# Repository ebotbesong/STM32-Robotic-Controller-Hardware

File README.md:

# STM32 Robotic Controller Hardware
This project introduces the design of a PCB board layout for robotics applications. The microcontroller used in the board design is the STM32F103C8T6. The STM32F103C8T6 is a medium density performance line ARM Cortex-M3 32bit microcontroller in the 48 pin LQFP package. It incorporates high performance RISC core with up to 72MHz operating frequency, high speed embedded memories, extensive range of enhanced I/Os and peripherals connected buses.

The designed board can be use as an alternative to the well known and documented Arduino and raspberry pie hardware. Also, the provided design can be modify to add more memory if needed. This however increases the complexity of the hardware.

## Isometric view
The MicroUSB is used but this can be change to USB type-C which is becoming the de facto standard nowadays.

 ## Top view
 There is provision for I2C and UART connector in the design. Therefore both the I2C and UART bus lines can be used for control interfaces.

## The PCB layout
The PCB layout was done using the KICAD EDA version 5.61 and the design is opensource. All design files are provided for download and can be found in the folder "docs" of the main repository shown above. Advanced version of the KICAD EDA can also be used to open the design files.

The project website is  https://ebotbesong.github.io/STM32-Robotic-Controller-Hardware/

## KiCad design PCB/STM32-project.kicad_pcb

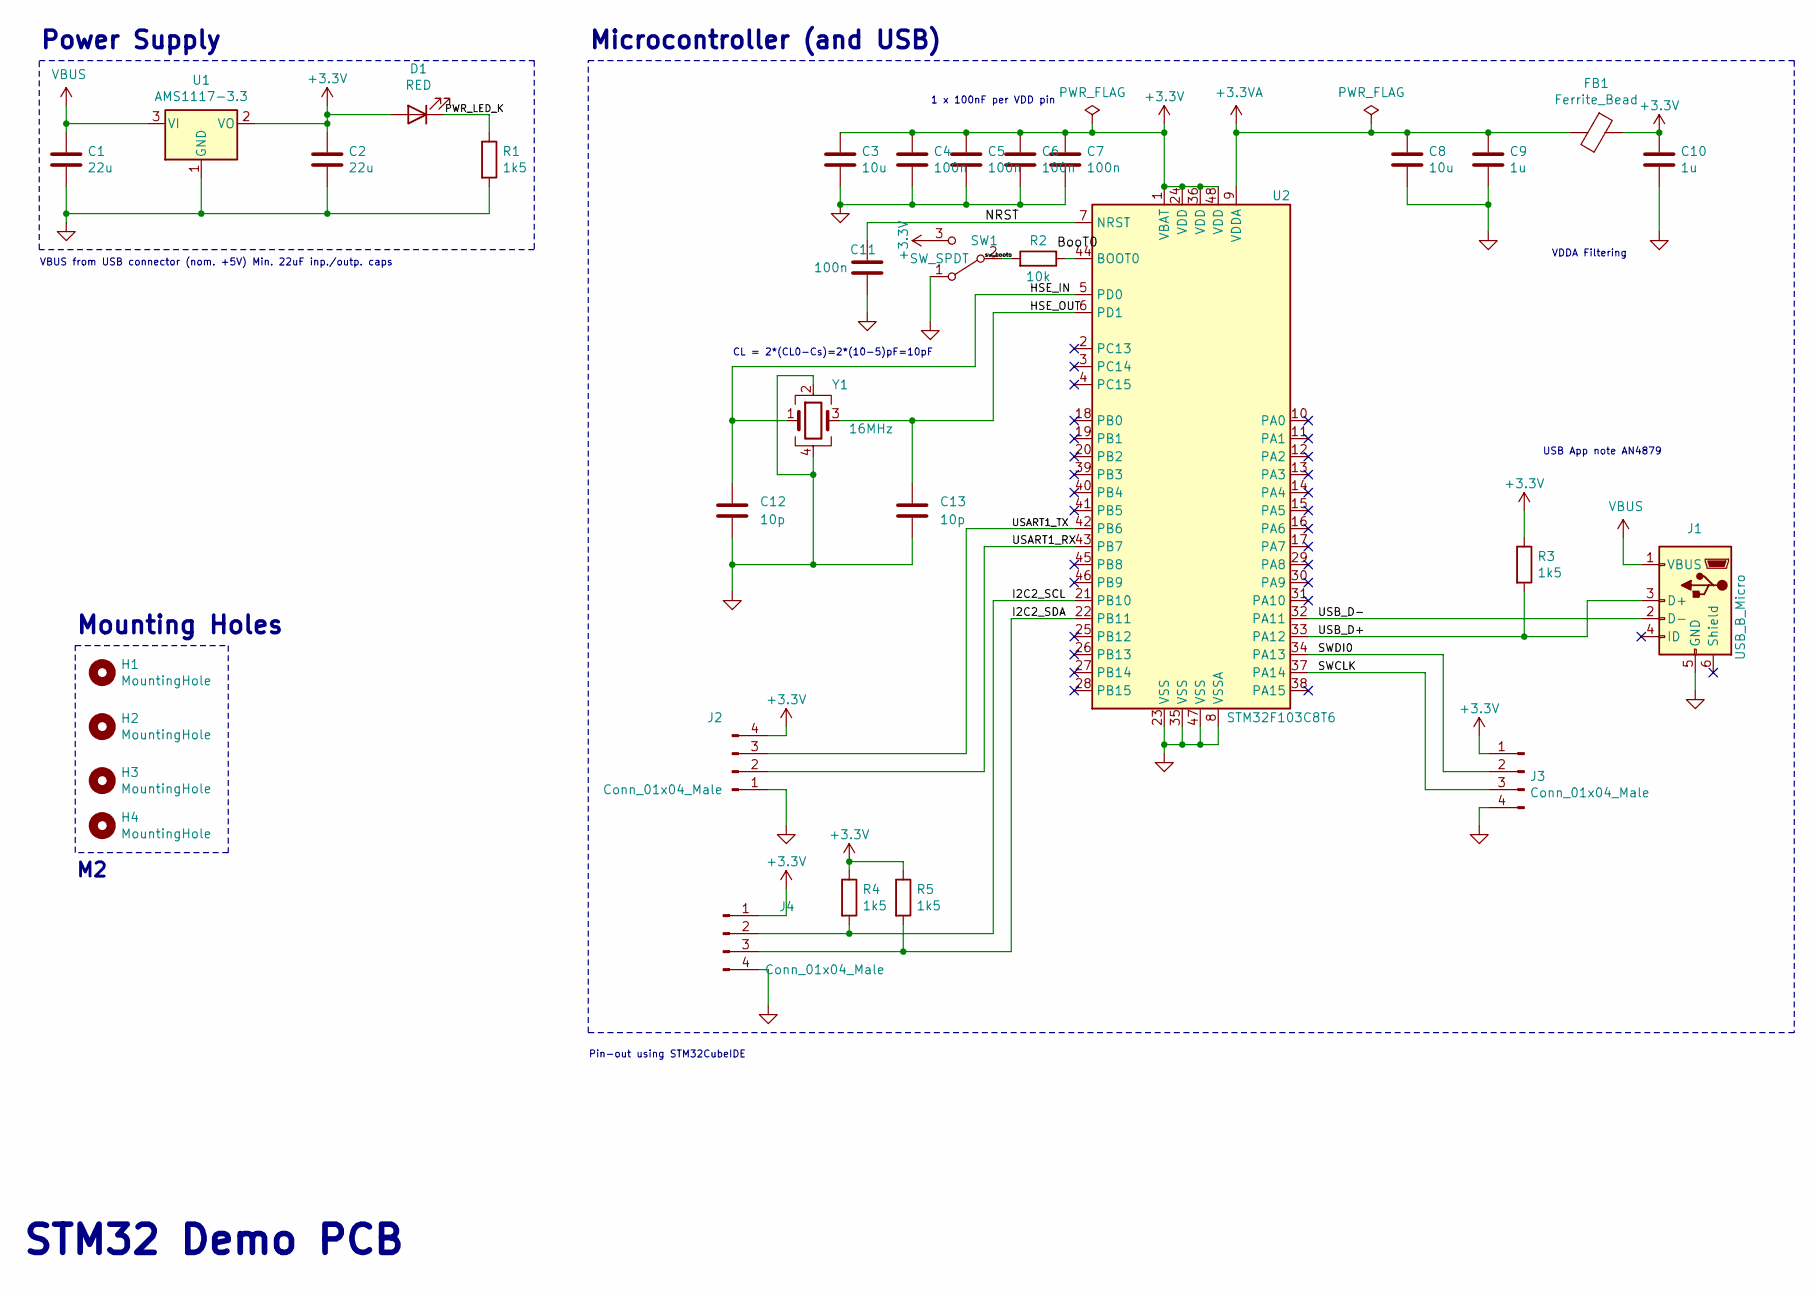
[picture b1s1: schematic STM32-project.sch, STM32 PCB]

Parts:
C1, C2: 22u; C_0805_2012Metric
C3: 10u; C_0603_1608Metric
C4, C5, C6, C7, C11: 100n; C_0402_1005Metric
C8: 10u; C_0402_1005Metric
C9, C10: 1u; C_0402_1005Metric
C12, C13: 10p; C_0402_1005Metric
D1: RED; LED_0603_1608Metric
FB1: Ferrite_Bead; L_0603_1608Metric
H1, H2, H3, H4: MountingHole; MountingHole_2.2mm_M2
J1: USB_B_Micro; USB_Micro-B_Wuerth_629105150521
J2, J3, J4: Conn_01x04_Male; PinHeader_1x04_P2.54mm_Vertical
R1, R3, R4, R5: 1k5; R_0402_1005Metric
R2: 10k; R_0402_1005Metric
SW1: SW_SPDT; SW_SPDT_PCM12
U1: AMS1117-3.3; SOT-223-3_TabPin2
U2: STM32F103C8T6; LQFP-48_7x7mm_P0.5mm
Y1: 16MHz; Crystal_SMD_0603-4Pin_6.0x3.5mm

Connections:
+3.3VA: C8.1, C9.1, FB1.2, U2.9 (VDDA)
+3V3: C2.1, C3.1, C4.1, C5.1, C6.1, C7.1, C10.1, D1.2 (A), FB1.1, J2.4, J3.1, J4.1, R3.1, R4.1, R5.1, SW1.3 (C), U1.2 (VO), U2.1 (VBAT), U2.24 (VDD), U2.36 (VDD), U2.48 (VDD)
/HSE_IN: C12.1, U2.5 (PD0), Y1.1
/HSE_OUT: C13.1, U2.6 (PD1), Y1.3
/I2C2_SCL: J4.2, R4.2, U2.21 (PB10)
/I2C2_SDA: J4.3, R5.2, U2.22 (PB11)
/NRST: C11.1, U2.7 (NRST)
/PWR_LED_K: D1.1 (K), R1.1
/SWCLK: J3.3, U2.37 (PA14)
/SWDI0: J3.2, U2.34 (PA13)
/USART1_RX: J2.2, U2.43 (PB7)
/USART1_TX: J2.3, U2.42 (PB6)
/USB_D+: J1.3 (D+), R3.2, U2.33 (PA12)
/USB_D-: J1.2 (D-), U2.32 (PA11)
GND: C1.2, C2.2, C3.2, C4.2, C5.2, C6.2, C7.2, C8.2, C9.2, C10.2, C11.2, C12.2, C13.2, J1.5 (GND), J2.1, J3.4, J4.4, R1.2, SW1.1 (A), U1.1 (GND), U2.8 (VSSA), U2.23 (VSS), U2.35 (VSS), U2.47 (VSS), Y1.2, Y1.4
unnamed: R2.1, U2.44 (BOOT0)
unnamed: R2.2, SW1.2 (B)
VBUS: C1.1, J1.1 (VBUS), U1.3 (VI)

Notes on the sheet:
Microcontroller (and USB)
STM32 Demo PCB
1 x 100nF per VDD pin
CL = 2*(CL0-Cs)=2*(10-5)pF=10pF
USB App note AN4879
VDDA Filtering
Pin-out using STM32CubeIDE
VBUS from USB connector (nom. +5V) Min. 22uF inp./outp. caps
Power Supply
Mounting Holes

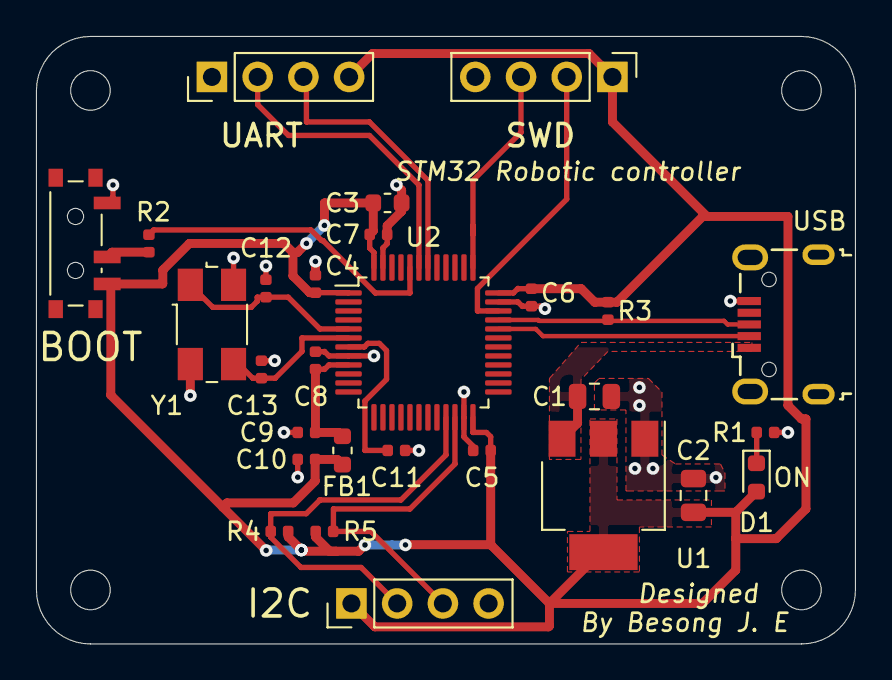
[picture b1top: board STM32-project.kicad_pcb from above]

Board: 2 copper layers, 45.5 x 33.8 mm, 32 parts (0 on the bottom side), 18 nets.

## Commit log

2022-03-08 :star: initial commit
2022-03-08 initial branch
2022-03-08 modefied the main pcb board. The power tracks
2022-03-08 changed image append from css to simple html
2022-03-08 created the image for pcb layout
2022-03-09 more descrition about the project is added to the README file
2022-03-09 corrent I/) to I/Os
2022-03-09 add more descrition
2022-03-09 cleaner description add
2022-03-12 modified the README file
2022-03-12 README modified`
2022-03-12 README modified
2022-03-12 readme
2022-03-14 Added BOM file
2022-03-14 Added project website Link
2022-03-20 README file
2022-03-21 README files
2022-03-21 README files modification
